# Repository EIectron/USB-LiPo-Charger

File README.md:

<div align="center">
  <b>
   <h1>
      4CH USB LiPo Charger
   </h1>
   <h6>
     V1
   </h6>
  </b>

</div>

### What is this project?
* 4CH USB LiPo Charger is charges 4 lipo batteries simultaneously via USB.
* You can choose separate charging current for each channel.
* Max 1.2A Charge current for each channel.
* Charge and Done Leds for each channel.
* JST-PH.2 connector and molex jst cable connection.

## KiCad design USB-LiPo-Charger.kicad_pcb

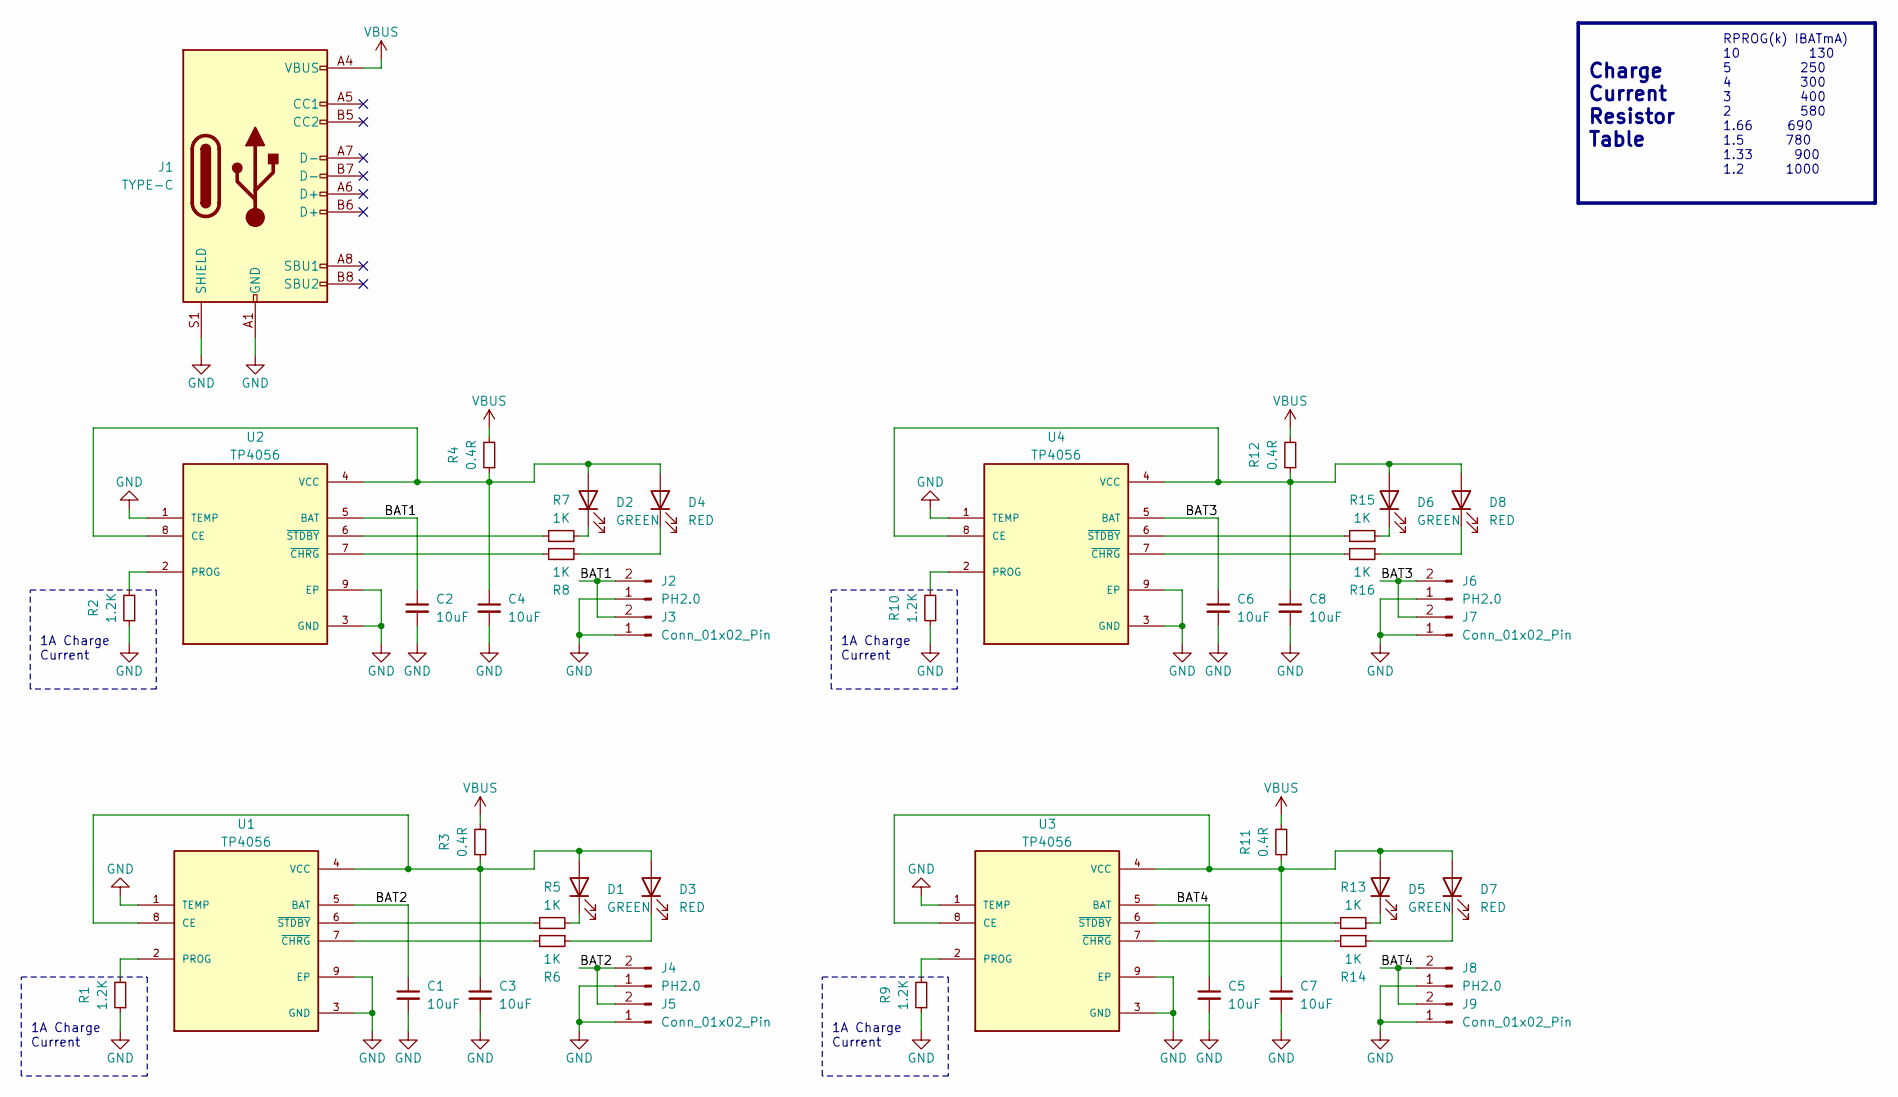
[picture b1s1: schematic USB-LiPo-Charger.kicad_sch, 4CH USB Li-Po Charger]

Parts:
C1, C2, C3, C4, C5, C6, C7, C8: 10uF; C_0603_1608Metric
D1, D2, D5, D6: GREEN; LED_0603_1608Metric
D3, D4, D7, D8: RED; LED_0603_1608Metric
J1: TYPE-C; USB_C_Receptacle_HRO_TYPE-C-31-M-12
J2, J4, J6, J8: PH2.0; JST_PH_B2B-PH-K_1x02_P2.00mm_Vertical
J3, J5, J7, J9: Conn_01x02_Pin; JST_VH_B2P-VH-FB-B_1x02_P3.96mm_Vertical
R1, R2, R9, R10: 1.2K; R_0603_1608Metric
R3, R4, R11, R12: 0.4R; R_2512_6332Metric
R5, R6, R7, R8, R13, R14, R15, R16: 1K; R_0603_1608Metric
U1, U2, U3, U4: TP4056; SOP127P600X175-9N

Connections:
/BAT1: C2.1, J2.2, J3.2, U2.5 (BAT)
/BAT2: C1.1, J4.2, J5.2, U1.5 (BAT)
/BAT3: C6.1, J6.2, J7.2, U4.5 (BAT)
/BAT4: C5.1, J8.2, J9.2, U3.5 (BAT)
GND: C1.2, C2.2, C3.2, C4.2, C5.2, C6.2, C7.2, C8.2, J1.A1 (GND), J1.A12 (GND), J1.B1 (GND), J1.B12 (GND), J1.S1 (SHIELD), J2.1, J3.1, J4.1, J5.1, J6.1, J7.1, J8.1, J9.1, R1.1, R2.1, R9.1, R10.1, U1.1 (TEMP), U1.3 (GND), U1.9 (EP), U2.1 (TEMP), U2.3 (GND), U2.9 (EP), U3.1 (TEMP), U3.3 (GND), U3.9 (EP), U4.1 (TEMP), U4.3 (GND), U4.9 (EP)
unnamed: C3.1, D1.2 (A), D3.2 (A), R3.1, U1.4 (VCC), U1.8 (CE)
unnamed: D1.1 (K), R5.2
unnamed: C4.1, D2.2 (A), D4.2 (A), R4.1, U2.4 (VCC), U2.8 (CE)
unnamed: D2.1 (K), R7.2
unnamed: D3.1 (K), R6.1
unnamed: D4.1 (K), R8.1
unnamed: C7.1, D5.2 (A), D7.2 (A), R11.1, U3.4 (VCC), U3.8 (CE)
unnamed: D5.1 (K), R13.2
unnamed: C8.1, D6.2 (A), D8.2 (A), R12.1, U4.4 (VCC), U4.8 (CE)
unnamed: D6.1 (K), R15.2
unnamed: D7.1 (K), R14.1
unnamed: D8.1 (K), R16.1
unnamed: R1.2, U1.2 (PROG)
unnamed: R6.2, U1.7 (~CHRG)
unnamed: R5.1, U1.6 (~STDBY)
unnamed: R2.2, U2.2 (PROG)
unnamed: R8.2, U2.7 (~CHRG)
unnamed: R7.1, U2.6 (~STDBY)
unnamed: R9.2, U3.2 (PROG)
unnamed: R14.2, U3.7 (~CHRG)
unnamed: R13.1, U3.6 (~STDBY)
unnamed: R10.2, U4.2 (PROG)
unnamed: R16.2, U4.7 (~CHRG)
unnamed: R15.1, U4.6 (~STDBY)
VBUS: J1.A4 (VBUS), J1.A9 (VBUS), J1.B4 (VBUS), J1.B9 (VBUS), R3.2, R4.2, R11.2, R12.2

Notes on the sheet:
1A Charge Current
RPROG(k) IBATmA) 10 130 5 250 4 300 3 400 2 580 1.66 690 1.5 780 1.33 900 1.2 1000
Charge Current Resistor Table

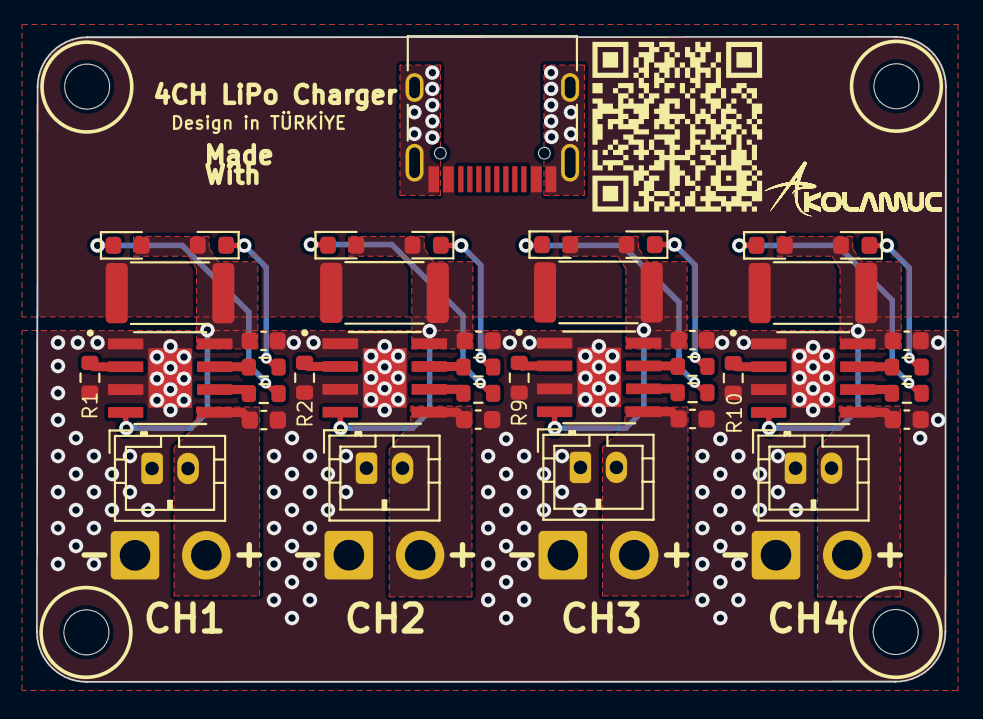
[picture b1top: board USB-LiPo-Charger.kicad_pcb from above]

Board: 2 copper layers, 50.5 x 35.8 mm, 45 parts (0 on the bottom side), 30 nets.

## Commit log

2024-04-13 Upload Files
